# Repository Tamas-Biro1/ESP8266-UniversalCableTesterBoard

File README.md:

## Overview
The Universal Cable Tester Board is a tool designed to test the continuity and proper wiring layout of any cables up to 32 wires. This project includes the design schematics, PCB layout, firmware, and software for the cable tester.

This board is not a standalone device, it must be connected to a computer (running Windows) through USB cable and the [Cable Analyzer](https://github.com/david-biro/UniversalCableAnalyzer) (opensource) must run on that machine. For more details about the software, click [here](https://github.com/david-biro/UniversalCableAnalyzer).

## How it works
### The hardware
The core of the Cable Tester board is a Wemos D1 Mini (ESP8266) microcontroller, which initiates the measurements, collects the test results, and sends the data back to the Cable Analyzer software running on the PC. The Cable Analyzer then evaluates the test results and visualizes them on the GUI. Communication is conducted via a USB connection, utilizing the UART port of the ESP8266, which is connected to a CH340 (or occasionally a CP2104) USB-to-Serial chip. This chip provides USB client connectivity to the ESP8266; therefore, it is required to install a serial port driver on the computer, for example from [here](http://www.wch-ic.com/downloads/CH341SER_ZIP.html).

The measuring mechanism is very simple: when the Cable Tester board receives the `<START>` string via serial, the microcontroller loops through the pins from 1 to 32 and applies 5V to them one by one. In every cycle, it measures and collects the response from the other side accordingly. When it reaches the last pin, it sends the result back to the Cable Tester application to evaluate and visualize.

Example cable layout and its serial output:

  ```
  <RESULT,3,8,4,16,34,0,0,0,0,0,0,0,0,0,0,0,0,0,0,0,0,0,0,0,0,0,0,0,0,0,0,0>
  ```
_Explanation:_ The output string is a comma-separated list of 32-bit integers containing the results for the pins from 1 to 32, listed from left to right respectively. By taking the binary representation of each value, the cable layout can be verified. See:

```
pin:                       [32]                             [1]  
                                       (binary)                  (decimal)
request sent on "A" side:  00000000 00000000 00000000 00000001       1
response got on "B" side:  00000000 00000000 00000000 00000011       3

request sent on "A" side:  00000000 00000000 00000000 00000010       2
response got on "B" side:  00000000 00000000 00000000 00001000       8

request sent on "A" side:  00000000 00000000 00000000 00000100       4
response got on "B" side:  00000000 00000000 00000000 00000100       4

request sent on "A" side:  00000000 00000000 00000000 00001000       8
response got on "B" side:  00000000 00000000 00000000 00010000       16

request sent on "A" side:  00000000 00000000 00000000 00010000       16
response got on "B" side:  00000000 00000000 00000000 00100010       34

request sent on "A" side:  00000000 00000000 00000000 00100000       32
response got on "B" side:  00000000 00000000 00000000 00000000       0

...

request sent on "A" side:  10000000 00000000 00000000 00000000   2147483648
response got on "B" side:  00000000 00000000 00000000 00000000       0
```

To understand this circuit, [here](https://wokwi.com/projects/403145055048695809) is an Arduino playground on **Wokwi** which simulates a straight cable (where pin 1 is connected to pin 1, pin 2 to pin 2, etc.). For better visualization, the wire "connections" are interrupted by LEDs, so when they flash, it means the checking is actually taking place.

Due to the lack of pins on ESP8622, shift registers are used on both side. On the `write` (or "A" side) 4 pcs of [74HC595](https://www.diodes.com/assets/Datasheets/74HC595.pdf) 8-bit serial-in/parallel-out shift registers are used in daisy chain to get 32-bit parallel output from the 32-bit serial input on the DS pin. On the `read` (or "B" side) 4 pcs of [74HC165](https://www.sparkfun.com/datasheets/Components/General/sn74hc165.pdf) parallel-in/serial-out shift registers are used. Between the `write` side and the green terminal blocks, 8 pcs of [IS281-4](https://docs.rs-online.com/c7c9/0900766b81617f80.pdf) NPN type optocouplers are used to isolate wires. 

### The firmware
The firmware is written in C++ using [PlatformIO](https://platformio.org/)

### Cable connector headers
Currently, only a 24 pin Molex PCB connector is included in this repo, future plans are to add more. Until that, every contributions are welcomed.

## Eagle files
The PCB is double-sided, contains only SMD components (except the 16 pcs through-hole terminal blocks). Here is the list of components:

| Qty | Component | Package |
|---|---|---|
| 4 | 74HC165D | SOIC-16 |
| 4 | 74HC595D | SOIC-16 |
| 8 | IS281 | SOIC-16 |
| 6 | BSS138BKW | SOT-323 |
| 16 | TH Terminal block | XY308-2.54-4P |
| 44 | 10 kΩ | R1206 |
| 32 | 407 Ω| R1206 |

For more details and LCSC partnumbers, please refer the partlist BOM file.

## Manufacturing
The final board was created by JLCPCB. For that the Gerber files, the LCSC partlist (BOM) and the Centroid (CPL) files are also included in this repo.

## Contributing
Every contributions are welcomed to improve the Universal Cable Tester. You can fork the repository and submit pull requests for any enhancements or bug fixes.

## License
This project is licensed under the GNU GPLv3 License - see the LICENSE file for details.

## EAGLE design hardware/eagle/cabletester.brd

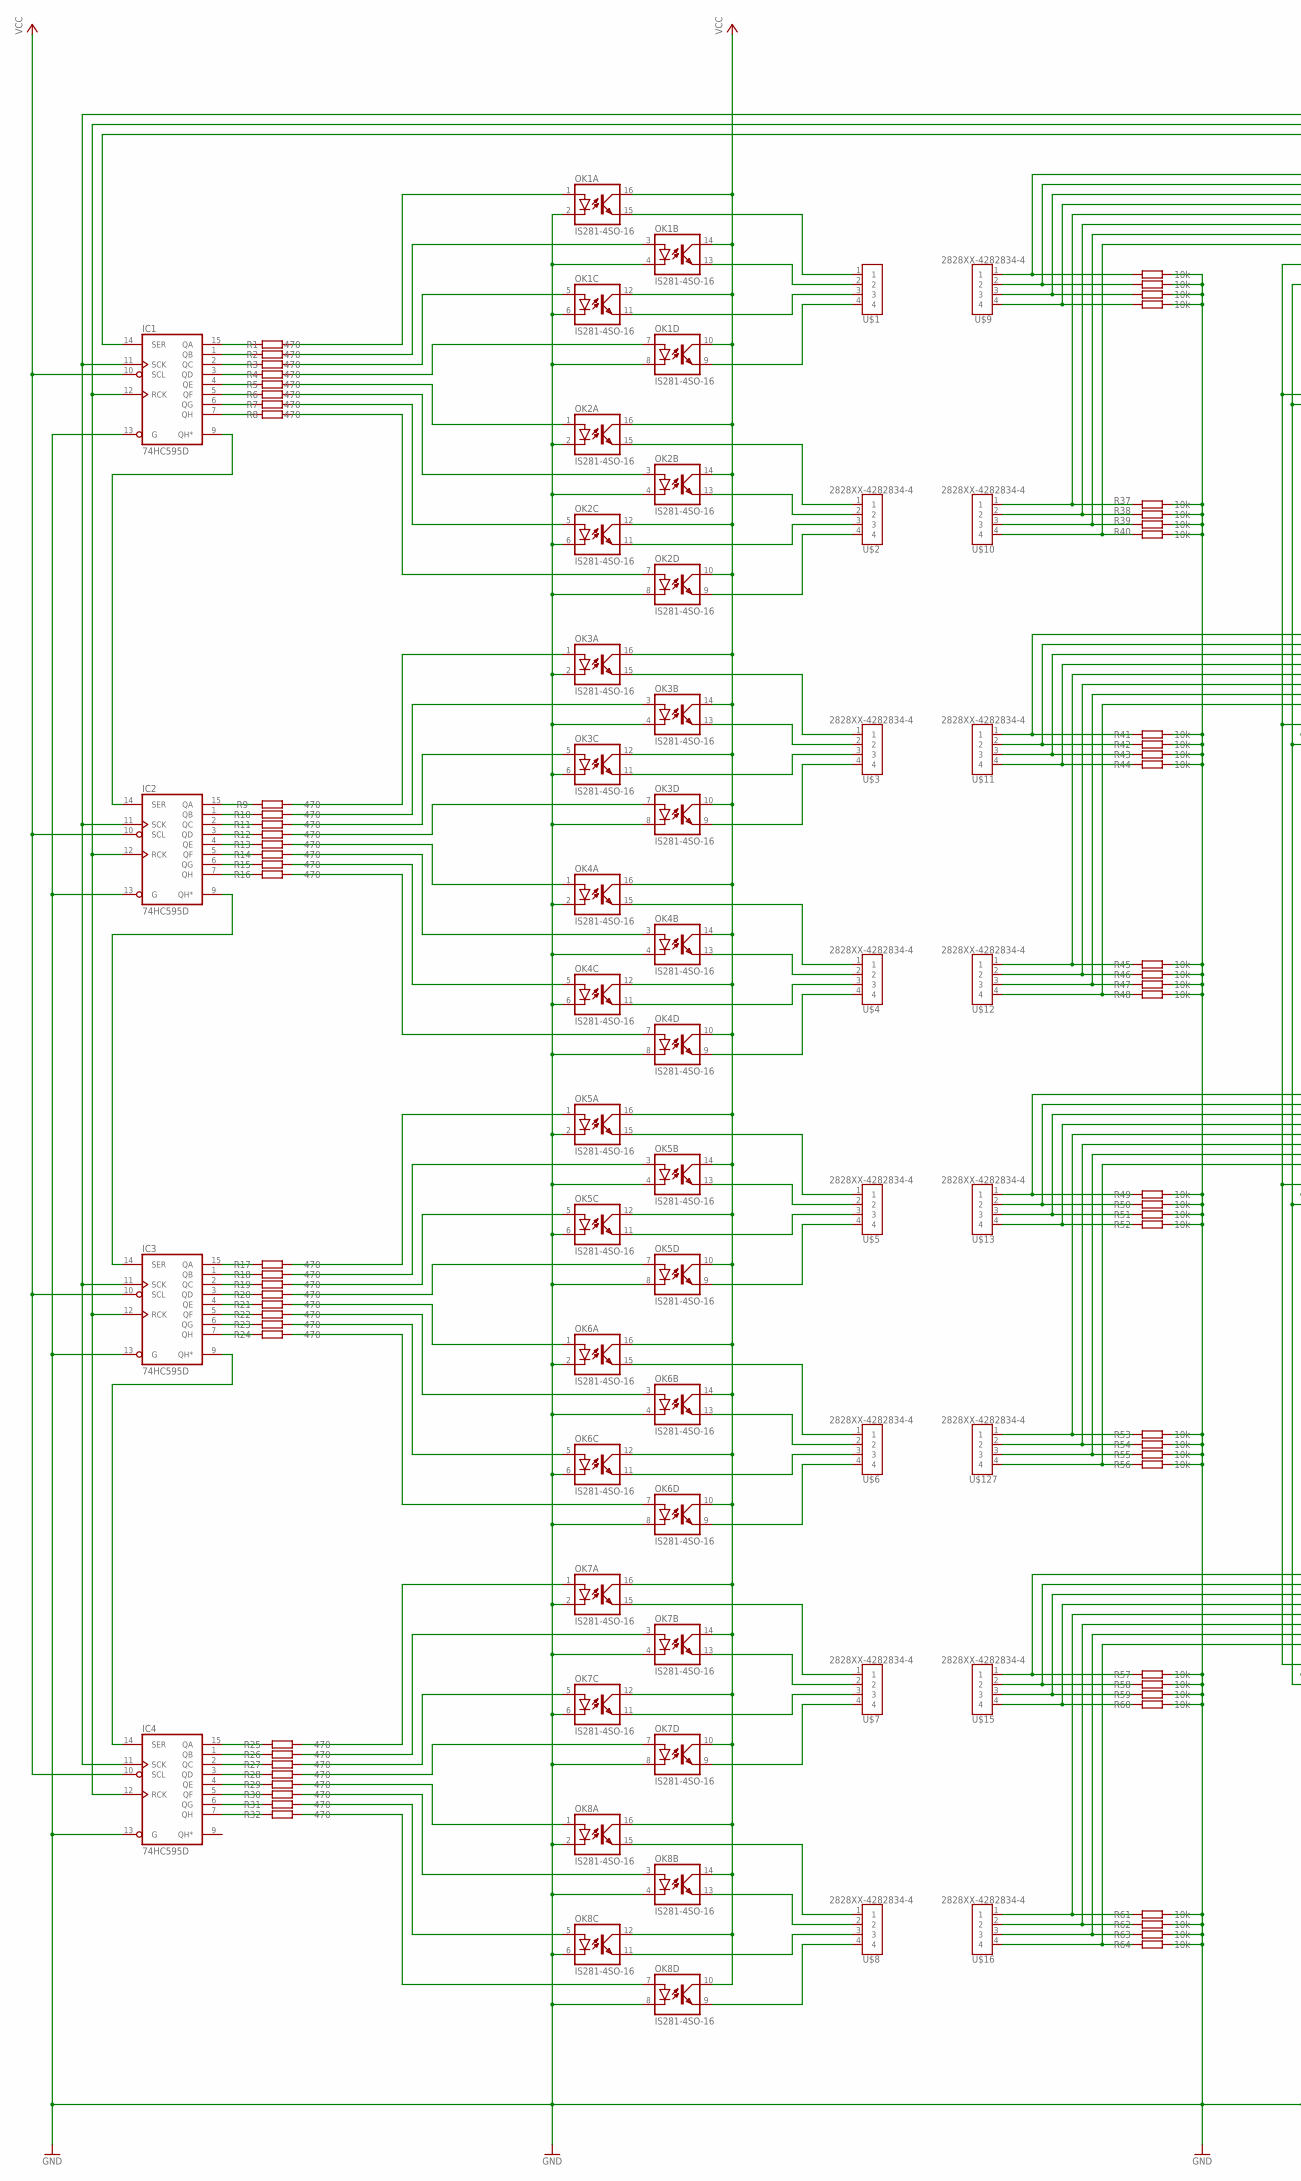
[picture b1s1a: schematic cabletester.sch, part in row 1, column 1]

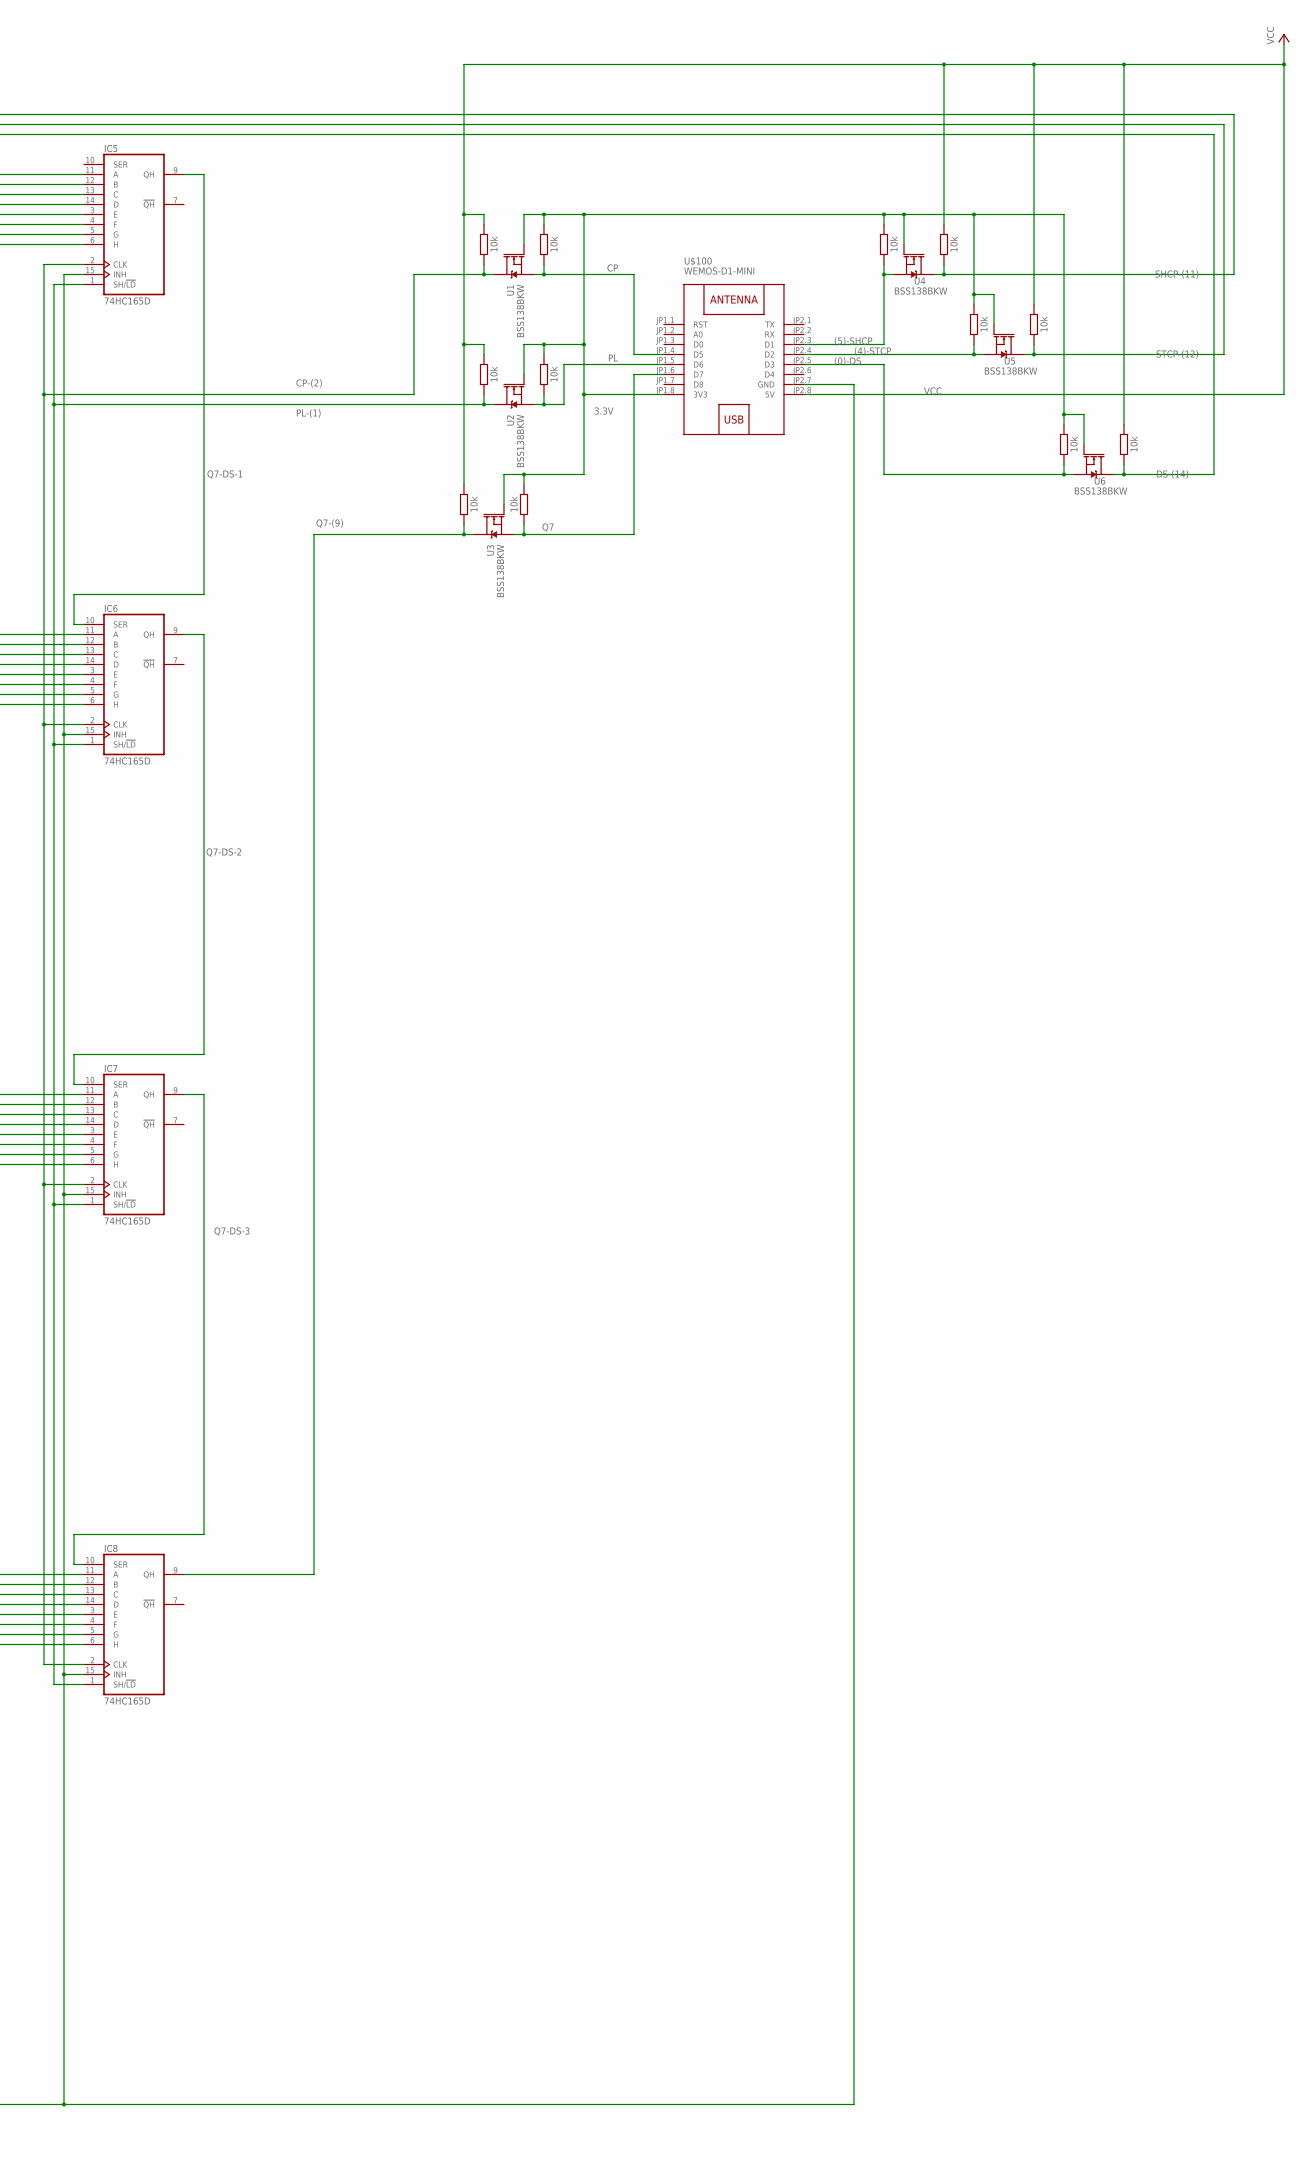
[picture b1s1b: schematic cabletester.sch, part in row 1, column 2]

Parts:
IC1, IC2, IC3, IC4: 74HC595D; SO16
IC5, IC6, IC7, IC8: 74HC165D; SO16
OK1, OK2, OK3, OK4, OK5, OK6, OK7, OK8: IS281-4SO-16; SO16
R1, R2, R3, R4, R5, R6, R7, R8, R9, R10, R11, R12, R13, R14, R15, R16, R17, R18, R19, R20, R21, R22, R23, R24, R25, R26, R27, R28, R29, R30, R31, R32: 470; RESC3216X70
R33, R34, R35, R36, R37, R38, R39, R40, R41, R42, R43, R44, R45, R46, R47, R48, R49, R50, R51, R52, R53, R54, R55, R56, R57, R58, R59, R60, R61, R62, R63, R64, R65, R66, R67, R68, R69, R70, R71, R72, R73, R74, R75, R76: 10k; RESC3216X70
U1, U2, U3, U4, U5, U6: BSS138BKW; SOT65P210X110-3N
U$1, U$2, U$3, U$4, U$5, U$6, U$7, U$8, U$9, U$10, U$11, U$12, U$13, U$15, U$16, U$127: 2828XX-4282834-4; TERMBLK_254-4N
U$100: WEMOS-D1-MINI

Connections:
3.3V: R66.2, R68.2, R70.1, R71.2, R73.2, R75.2, U1.1 (G), U2.1 (G), U3.1 (G), U4.1 (G), U5.1 (G), U6.1 (G), U$100.JP1.8 (3V3)
(0)-DS: R75.1, U6.2 (S), U$100.JP2.5 (D3)
(4)-STCP: R73.1, U5.2 (S), U$100.JP2.4 (D2)
(5)-SHCP: R71.1, U4.2 (S), U$100.JP2.3 (D1)
CP: R66.1, U1.2 (S), U$100.JP1.4 (D5)
CP-(2): IC5.2 (CLK), IC6.2 (CLK), IC7.2 (CLK), IC8.2 (CLK), R65.1, U1.3 (D)
DS-(14): IC1.14 (SER), R76.1, U6.3 (D)
GND: IC1.8 (GND), IC1.13 (G), IC2.8 (GND), IC2.13 (G), IC3.8 (GND), IC3.13 (G), IC4.8 (GND), IC4.13 (G), IC5.8 (GND), IC5.15 (INH), IC6.8 (GND), IC6.15 (INH), IC7.8 (GND), IC7.15 (INH), IC8.8 (GND), IC8.15 (INH), OK1.2 (C), OK1.4 (C), OK1.6 (C), OK1.8 (C), OK2.2 (C), OK2.4 (C), OK2.6 (C), OK2.8 (C), OK3.2 (C), OK3.4 (C), OK3.6 (C), OK3.8 (C), OK4.2 (C), OK4.4 (C), OK4.6 (C), OK4.8 (C), OK5.2 (C), OK5.4 (C), OK5.6 (C), OK5.8 (C), OK6.2 (C), OK6.4 (C), OK6.6 (C), OK6.8 (C), OK7.2 (C), OK7.4 (C), OK7.6 (C), OK7.8 (C), OK8.2 (C), OK8.4 (C), OK8.6 (C), OK8.8 (C), R33.2, R34.2, R35.2, R36.2, R37.2, R38.2, R39.2, R40.2, R41.2, R42.2, R43.2, R44.2, R45.2, R46.2, R47.2, R48.2, R49.2, R50.2, R51.2, R52.2, R53.2, R54.2, R55.2, R56.2, R57.2, R58.2, R59.2, R60.2, R61.2, R62.2, R63.2, R64.2, U$100.JP2.7 (GND)
unnamed: IC4.1 (QB), R26.1
unnamed: IC1.9 (QH*), IC2.14 (SER)
unnamed: IC2.9 (QH*), IC3.14 (SER)
unnamed: IC3.9 (QH*), IC4.14 (SER)
unnamed: OK7.1 (A), R25.2
unnamed: IC1.6 (QG), R7.1
unnamed: IC1.5 (QF), R6.1
unnamed: IC1.4 (QE), R5.1
unnamed: IC1.3 (QD), R4.1
unnamed: IC1.2 (QC), R3.1
unnamed: IC1.1 (QB), R2.1
unnamed: IC1.15 (QA), R1.1
unnamed: IC1.7 (QH), R8.1
unnamed: OK1.1 (A), R1.2
unnamed: OK1.3 (A), R2.2
unnamed: OK1.5 (A), R3.2
unnamed: OK1.7 (A), R4.2
unnamed: OK2.1 (A), R5.2
unnamed: OK2.3 (A), R6.2
unnamed: OK1.15 (EMIT), U$1.1
unnamed: OK1.13 (EMIT), U$1.2
unnamed: OK1.11 (EMIT), U$1.3
unnamed: OK1.9 (EMIT), U$1.4
unnamed: OK2.15 (EMIT), U$2.1
unnamed: OK2.13 (EMIT), U$2.2
unnamed: OK2.11 (EMIT), U$2.3
unnamed: OK2.9 (EMIT), U$2.4
unnamed: OK2.5 (A), R7.2
unnamed: OK2.7 (A), R8.2
unnamed: IC2.1 (QB), R10.1
unnamed: IC2.2 (QC), R11.1
unnamed: IC2.3 (QD), R12.1
unnamed: IC2.4 (QE), R13.1
unnamed: IC2.5 (QF), R14.1
unnamed: IC2.6 (QG), R15.1
unnamed: IC2.7 (QH), R16.1
unnamed: IC2.15 (QA), R9.1
unnamed: OK3.1 (A), R9.2
unnamed: OK3.3 (A), R10.2
unnamed: OK3.5 (A), R11.2
unnamed: OK3.7 (A), R12.2
unnamed: OK4.1 (A), R13.2
unnamed: OK4.3 (A), R14.2
unnamed: OK4.5 (A), R15.2
unnamed: OK4.7 (A), R16.2
unnamed: IC3.6 (QG), R23.1
unnamed: IC3.5 (QF), R22.1
unnamed: IC3.4 (QE), R21.1
unnamed: IC3.3 (QD), R20.1
unnamed: IC3.2 (QC), R19.1
unnamed: IC3.1 (QB), R18.1
unnamed: IC3.7 (QH), R24.1
unnamed: IC3.15 (QA), R17.1
unnamed: OK5.1 (A), R17.2
unnamed: OK5.3 (A), R18.2
unnamed: OK5.5 (A), R19.2
unnamed: OK5.7 (A), R20.2
unnamed: OK6.1 (A), R21.2
unnamed: OK6.3 (A), R22.2
unnamed: OK6.5 (A), R23.2
unnamed: OK6.7 (A), R24.2
unnamed: OK7.3 (A), R26.2
unnamed: OK7.5 (A), R27.2
unnamed: OK7.7 (A), R28.2
unnamed: OK8.1 (A), R29.2
unnamed: OK3.15 (EMIT), U$3.1
unnamed: OK3.13 (EMIT), U$3.2
unnamed: OK3.11 (EMIT), U$3.3
unnamed: OK3.9 (EMIT), U$3.4
unnamed: OK4.15 (EMIT), U$4.1
unnamed: OK4.13 (EMIT), U$4.2
unnamed: OK4.11 (EMIT), U$4.3
unnamed: OK4.9 (EMIT), U$4.4
unnamed: OK5.15 (EMIT), U$5.1
unnamed: OK5.13 (EMIT), U$5.2
unnamed: OK5.11 (EMIT), U$5.3
unnamed: OK5.9 (EMIT), U$5.4
unnamed: OK6.15 (EMIT), U$6.1
unnamed: OK6.13 (EMIT), U$6.2
unnamed: OK6.11 (EMIT), U$6.3
unnamed: OK6.9 (EMIT), U$6.4
unnamed: IC5.11 (A), R33.1, U$9.1
unnamed: IC6.11 (A), R41.1, U$11.1
unnamed: IC5.13 (C), R35.1, U$9.3
unnamed: IC5.14 (D), R36.1, U$9.4
unnamed: IC5.12 (B), R34.1, U$9.2
unnamed: IC6.12 (B), R42.1, U$11.2
unnamed: IC5.3 (E), R37.1, U$10.1
unnamed: IC5.4 (F), R38.1, U$10.2
unnamed: IC5.5 (G), R39.1, U$10.3
unnamed: IC5.6 (H), R40.1, U$10.4
unnamed: IC6.13 (C), R43.1, U$11.3
unnamed: IC6.14 (D), R44.1, U$11.4
unnamed: IC6.3 (E), R45.1, U$12.1
unnamed: IC6.4 (F), R46.1, U$12.2
unnamed: IC6.5 (G), R47.1, U$12.3
unnamed: IC6.6 (H), R48.1, U$12.4
unnamed: IC7.11 (A), R49.1, U$13.1
unnamed: IC7.12 (B), R50.1, U$13.2
unnamed: IC7.13 (C), R51.1, U$13.3
unnamed: IC7.14 (D), R52.1, U$13.4
unnamed: IC7.3 (E), R53.1, U$127.1
unnamed: IC7.4 (F), R54.1, U$127.2
unnamed: IC7.5 (G), R55.1, U$127.3
unnamed: IC7.6 (H), R56.1, U$127.4
unnamed: OK8.3 (A), R30.2
unnamed: OK8.5 (A), R31.2
unnamed: OK8.7 (A), R32.2
unnamed: IC4.2 (QC), R27.1
unnamed: IC4.3 (QD), R28.1
unnamed: IC4.4 (QE), R29.1
unnamed: IC4.5 (QF), R30.1
unnamed: IC4.6 (QG), R31.1
unnamed: IC4.7 (QH), R32.1
unnamed: IC4.15 (QA), R25.1
unnamed: OK7.15 (EMIT), U$7.1
unnamed: OK7.13 (EMIT), U$7.2
unnamed: OK7.11 (EMIT), U$7.3
unnamed: OK7.9 (EMIT), U$7.4
unnamed: OK8.15 (EMIT), U$8.1
unnamed: OK8.13 (EMIT), U$8.2
unnamed: OK8.11 (EMIT), U$8.3
unnamed: OK8.9 (EMIT), U$8.4
unnamed: IC8.11 (A), R57.1, U$15.1
unnamed: IC8.12 (B), R58.1, U$15.2
unnamed: IC8.13 (C), R59.1, U$15.3
unnamed: IC8.14 (D), R60.1, U$15.4
unnamed: IC8.3 (E), R61.1, U$16.1
unnamed: IC8.4 (F), R62.1, U$16.2
unnamed: IC8.5 (G), R63.1, U$16.3
unnamed: IC8.6 (H), R64.1, U$16.4
PL: R68.1, U2.2 (S), U$100.JP1.5 (D6)
PL-(1): IC5.1 (SH/!LD), IC6.1 (SH/!LD), IC7.1 (SH/!LD), IC8.1 (SH/!LD), R67.1, U2.3 (D)
Q7: R70.2, U3.2 (S), U$100.JP1.6 (D7)
Q7-(9): IC8.9 (QH), R69.1, U3.3 (D)
Q7-DS-1: IC5.9 (QH), IC6.10 (SER)
Q7-DS-2: IC6.9 (QH), IC7.10 (SER)
Q7-DS-3: IC7.9 (QH), IC8.10 (SER)
SHCP-(11): IC1.11 (SCK), IC2.11 (SCK), IC3.11 (SCK), IC4.11 (SCK), R72.1, U4.3 (D)
STCP-(12): IC1.12 (RCK), IC2.12 (RCK), IC3.12 (RCK), IC4.12 (RCK), R74.1, U5.3 (D)
VCC: IC1.10 (SCL), IC1.16 (VCC), IC2.10 (SCL), IC2.16 (VCC), IC3.10 (SCL), IC3.16 (VCC), IC4.10 (SCL), IC4.16 (VCC), IC5.16 (VCC), IC6.16 (VCC), IC7.16 (VCC), IC8.16 (VCC), OK1.10 (COL), OK1.12 (COL), OK1.14 (COL), OK1.16 (COL), OK2.10 (COL), OK2.12 (COL), OK2.14 (COL), OK2.16 (COL), OK3.10 (COL), OK3.12 (COL), OK3.14 (COL), OK3.16 (COL), OK4.10 (COL), OK4.12 (COL), OK4.14 (COL), OK4.16 (COL), OK5.10 (COL), OK5.12 (COL), OK5.14 (COL), OK5.16 (COL), OK6.10 (COL), OK6.12 (COL), OK6.14 (COL), OK6.16 (COL), OK7.10 (COL), OK7.12 (COL), OK7.14 (COL), OK7.16 (COL), OK8.10 (COL), OK8.12 (COL), OK8.14 (COL), OK8.16 (COL), R65.2, R67.2, R69.2, R72.2, R74.2, R76.2, U$100.JP2.8 (5V)

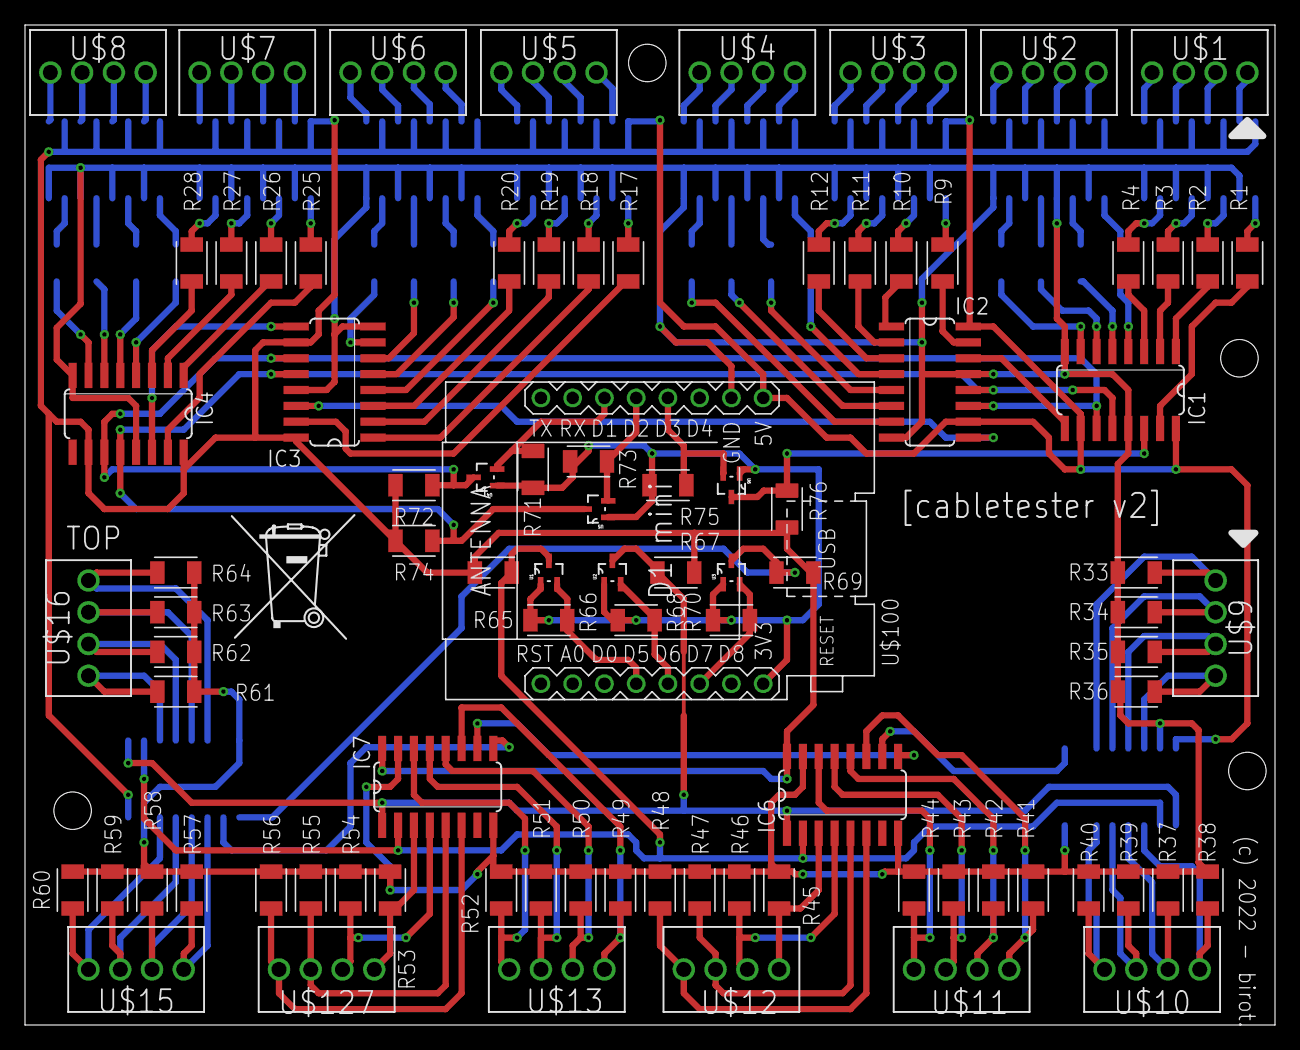
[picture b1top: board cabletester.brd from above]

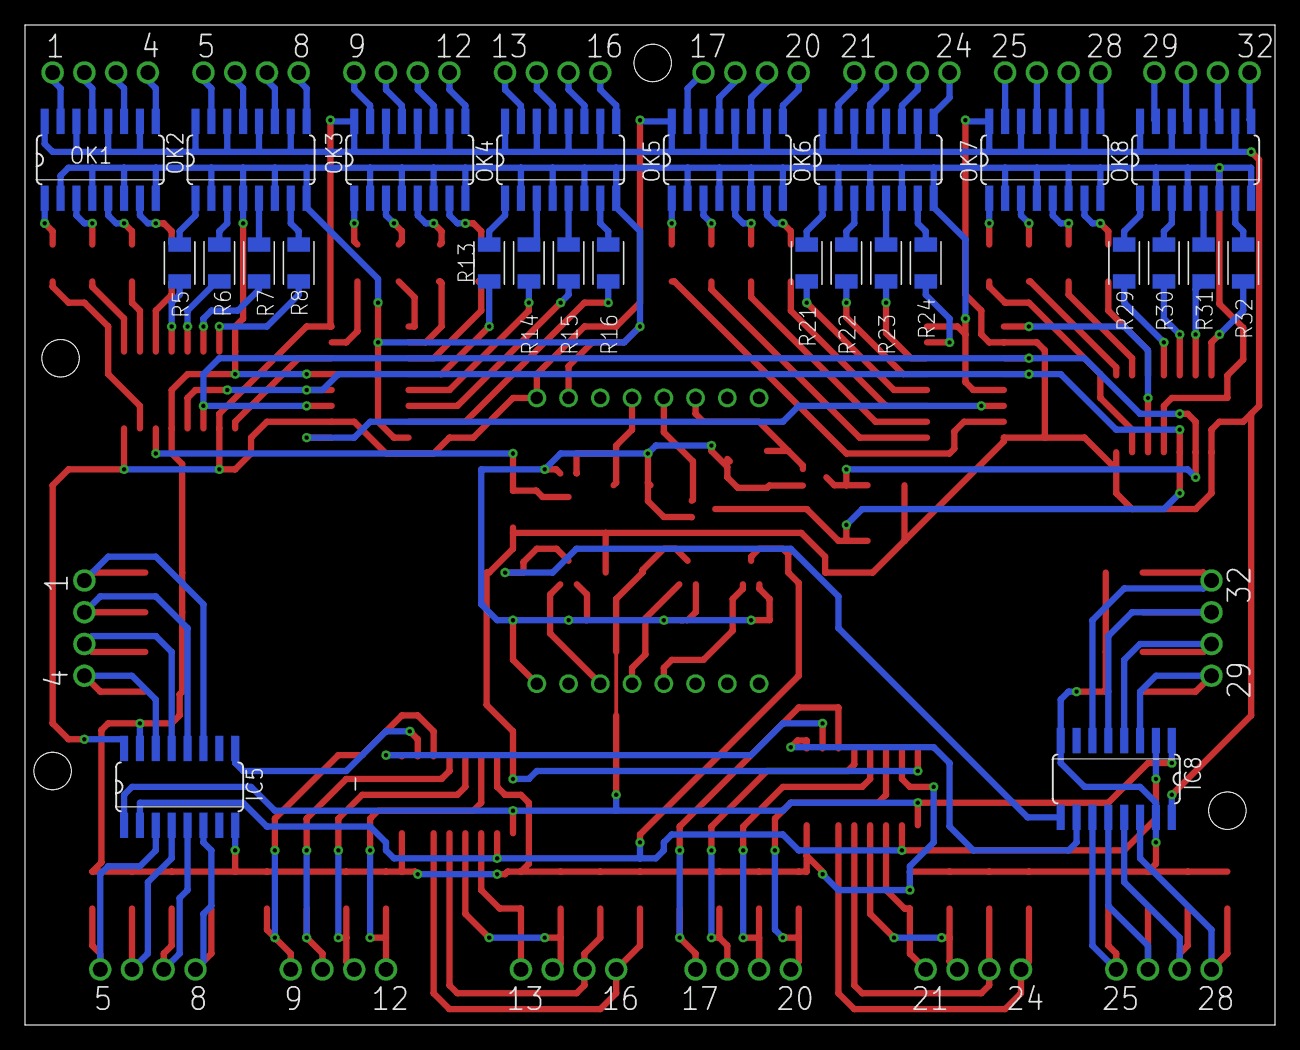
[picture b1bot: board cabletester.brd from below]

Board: 2 copper layers, 100.0 x 80.0 mm, 116 parts (26 on the bottom side), 149 nets.

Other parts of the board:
U$14: MUELLTONNE_10.00

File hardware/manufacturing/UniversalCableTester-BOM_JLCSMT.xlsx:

Comment | Designator | Footprint | JLCPCB Part #（optional）
74HC165D | IC5 | SO16 | C5613
74HC165D | IC8 | SO16 | C5613
IS281-4SO-16 | OK1 | SO16 | C89878
IS281-4SO-16 | OK2 | SO16 | C89878
IS281-4SO-16 | OK3 | SO16 | C89878
IS281-4SO-16 | OK4 | SO16 | C89878
IS281-4SO-16 | OK5 | SO16 | C89878
IS281-4SO-16 | OK6 | SO16 | C89878
IS281-4SO-16 | OK7 | SO16 | C89878
IS281-4SO-16 | OK8 | SO16 | C89878
470 | R13 | R1206 | C4502
470 | R14 | R1206 | C4502
470 | R15 | R1206 | C4502
470 | R16 | R1206 | C4502
470 | R21 | R1206 | C4502
470 | R22 | R1206 | C4502
470 | R23 | R1206 | C4502
470 | R24 | R1206 | C4502
470 | R29 | R1206 | C4502
470 | R30 | R1206 | C4502
470 | R31 | R1206 | C4502
470 | R32 | R1206 | C4502
470 | R5 | R1206 | C4502
470 | R6 | R1206 | C4502
470 | R7 | R1206 | C4502
470 | R8 | R1206 | C4502
74HC595D | IC1 | SO16 | C5947
74HC595D | IC2 | SO16 | C5947
74HC595D | IC3 | SO16 | C5947
74HC595D | IC4 | SO16 | C5947
74HC165D | IC6 | SO16 | C5613
74HC165D | IC7 | SO16 | C5613
470 | R1 | R1206 | C4502
470 | R10 | R1206 | C4502
470 | R11 | R1206 | C4502
470 | R12 | R1206 | C4502
470 | R17 | R1206 | C4502
470 | R18 | R1206 | C4502
470 | R19 | R1206 | C4502
470 | R2 | R1206 | C4502
470 | R20 | R1206 | C4502
470 | R25 | R1206 | C4502
470 | R26 | R1206 | C4502
470 | R27 | R1206 | C4502
470 | R28 | R1206 | C4502
470 | R3 | R1206 | C4502
10k | R33 | R1206 | C17902
10k | R34 | R1206 | C17902
10k | R35 | R1206 | C17902
10k | R36 | R1206 | C17902
10k | R37 | R1206 | C17902
10k | R38 | R1206 | C17902
10k | R39 | R1206 | C17902
470 | R4 | R1206 | C4502
10k | R40 | R1206 | C17902
10k | R41 | R1206 | C17902
10k | R42 | R1206 | C17902
10k | R43 | R1206 | C17902
10k | R44 | R1206 | C17902
10k | R45 | R1206 | C17902
10k | R46 | R1206 | C17902
10k | R47 | R1206 | C17902
10k | R48 | R1206 | C17902
10k | R49 | R1206 | C17902
10k | R50 | R1206 | C17902
10k | R51 | R1206 | C17902
10k | R52 | R1206 | C17902
10k | R53 | R1206 | C17902
10k | R54 | R1206 | C17902
10k | R55 | R1206 | C17902
10k | R56 | R1206 | C17902
10k | R57 | R1206 | C17902
10k | R58 | R1206 | C17902
10k | R59 | R1206 | C17902
10k | R60 | R1206 | C17902
10k | R61 | R1206 | C17902
10k | R62 | R1206 | C17902
10k | R63 | R1206 | C17902
10k | R64 | R1206 | C17902
10k | R65 | R1206 | C17902
10k | R66 | R1206 | C17902
10k | R67 | R1206 | C17902
10k | R68 | R1206 | C17902
10k | R69 | R1206 | C17902
10k | R70 | R1206 | C17902
10k | R71 | R1206 | C17902
10k | R72 | R1206 | C17902
10k | R73 | R1206 | C17902
10k | R74 | R1206 | C17902
10k | R75 | R1206 | C17902
10k | R76 | R1206 | C17902
470 | R9 | R1206 | C4502
BSS138BKW | U1 | SOT65P210X110-3N | C5224281
BSS138BKW | U2 | SOT65P210X110-3N | C5224281
BSS138BKW | U3 | SOT65P210X110-3N | C5224281
BSS138BKW | U4 | SOT65P210X110-3N | C5224281
BSS138BKW | U5 | SOT65P210X110-3N | C5224281
BSS138BKW | U6 | SOT65P210X110-3N | C5224281
TERMBLK_254-4N | U$1 | 2828XX-4282834-4 | C915913
TERMBLK_254-4N | U$2 | 2828XX-4282834-4 | C915913
TERMBLK_254-4N | U$3 | 2828XX-4282834-4 | C915913
TERMBLK_254-4N | U$4 | 2828XX-4282834-4 | C915913
TERMBLK_254-4N | U$5 | 2828XX-4282834-4 | C915913
TERMBLK_254-4N | U$6 | 2828XX-4282834-4 | C915913
TERMBLK_254-4N | U$7 | 2828XX-4282834-4 | C915913
TERMBLK_254-4N | U$8 | 2828XX-4282834-4 | C915913
TERMBLK_254-4N | U$9 | 2828XX-4282834-4 | C915913
TERMBLK_254-4N | U$10 | 2828XX-4282834-4 | C915913
TERMBLK_254-4N | U$11 | 2828XX-4282834-4 | C915913
TERMBLK_254-4N | U$12 | 2828XX-4282834-4 | C915913
TERMBLK_254-4N | U$13 | 2828XX-4282834-4 | C915913
TERMBLK_254-4N | U$15 | 2828XX-4282834-4 | C915913
TERMBLK_254-4N | U$16 | 2828XX-4282834-4 | C915913
TERMBLK_254-4N | U$127 | 2828XX-4282834-4 | C915913

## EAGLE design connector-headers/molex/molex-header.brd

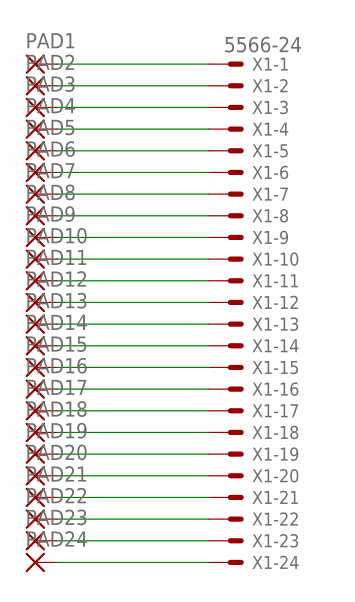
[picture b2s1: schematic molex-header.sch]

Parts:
PAD1, PAD2, PAD3, PAD4, PAD5, PAD6, PAD7, PAD8, PAD9, PAD10, PAD11, PAD12, PAD13, PAD14, PAD15, PAD16, PAD17, PAD18, PAD19, PAD20, PAD21, PAD22, PAD23, PAD24: SMD5; SMD2,54-5,08
X1: 5566-24

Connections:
unnamed: PAD1.1, X1.1
unnamed: PAD2.1, X1.2
unnamed: PAD3.1, X1.3
unnamed: PAD4.1, X1.4
unnamed: PAD5.1, X1.5
unnamed: PAD6.1, X1.6
unnamed: PAD7.1, X1.7
unnamed: PAD8.1, X1.8
unnamed: PAD9.1, X1.9
unnamed: PAD10.1, X1.10
unnamed: PAD11.1, X1.11
unnamed: PAD12.1, X1.12
unnamed: PAD13.1, X1.13
unnamed: PAD14.1, X1.14
unnamed: PAD15.1, X1.15
unnamed: PAD16.1, X1.16
unnamed: PAD17.1, X1.17
unnamed: PAD18.1, X1.18
unnamed: PAD19.1, X1.19
unnamed: PAD20.1, X1.20
unnamed: PAD21.1, X1.21
unnamed: PAD22.1, X1.22
unnamed: PAD23.1, X1.23
unnamed: PAD24.1, X1.24

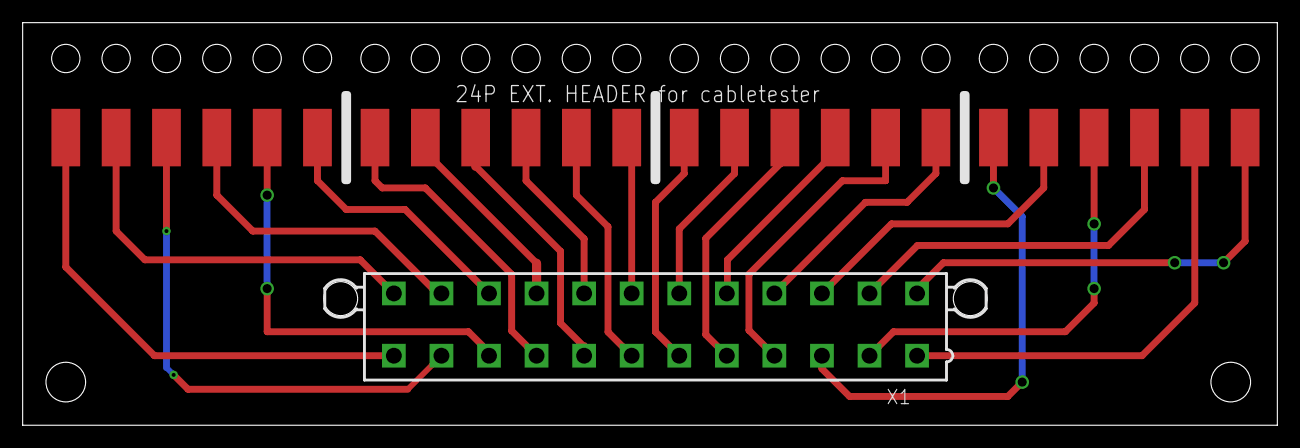
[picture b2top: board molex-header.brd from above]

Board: 2 copper layers, 110.8 x 35.5 mm, 25 parts (0 on the bottom side), 24 nets.

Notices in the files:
hardware/eagle/cabletester.brd:
(c) 2022 - birot.
parts and their libraries:
diy-modules: Released under the Creative Commons Attribution 4.0 International License: http://creativecommons.org/licenses/by/4.0
